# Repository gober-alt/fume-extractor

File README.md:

# Fume Extractor
A simple fume extractor with adjustable fan speed.
# PCB + Schematic
Simple board for controlling fan speed!

# BOM
Materials used:
- x1 15x15 JLCPCB shipping box
- x3 Helping hands arms
- x1 Custom PCB for fan control
- x1 BD139 Transistor
- x1 120mm 12V fan
- x1 female JST PH 2.0 connector
- x1 10k Potentionmeter
- x1 12V Power supply
- x1 Activated carbon filter sheet
- x1 1k Resistor
- Any paperweight, I used glass fairy stones!

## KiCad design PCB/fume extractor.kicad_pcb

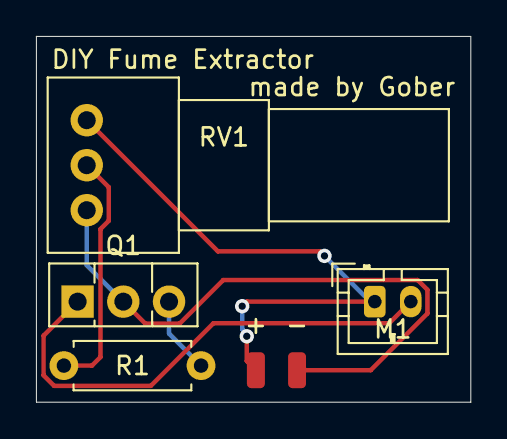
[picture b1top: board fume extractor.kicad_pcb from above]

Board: 2 copper layers, 24.1 x 20.3 mm, 6 parts (0 on the bottom side), 5 nets.

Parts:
+: +; SolderWirePad_1x01_SMD_1x2mm
-: -; SolderWirePad_1x01_SMD_1x2mm
M1: Fan; JST_PH_B2B-PH-K_1x02_P2.00mm_Vertical
Q1: BD139; TO-126-3_Vertical
R1: 1k; R_Axial_DIN0207_L6.3mm_D2.5mm_P7.62mm_Horizontal
RV1: R_POT; Potentiometer_Alps_RK097_Single_Horizontal

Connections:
unnamed: +.1, M1.1, RV1.3
unnamed: -.1, Q1.2, RV1.1
unnamed: M1.2, Q1.1
unnamed: Q1.3, R1.1
unnamed: R1.2, RV1.2

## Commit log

2026-04-06 Create blibz
2026-04-06 Create blibz2
2026-04-06 Rename pcb.PNG to Assets/pcb.PNG
2026-04-06 Rename schematic.PNG to Assets/schematic.PNG
2026-04-06 Rename Assets/pcb.PNG to pcb.PNG
2026-04-06 Rename Assets/schematic.PNG to schematic.PNG
2026-04-06 Rename pcb.PNG to pcb.png
2026-04-06 Rename schematic.PNG to schematic.png
